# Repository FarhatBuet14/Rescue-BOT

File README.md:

# Rescue-BOT
It is a mechanical system of four wheeled car with two artificial hands. It has also raspberry pi with a pi camera for image processing. The purpose of this project is to rescue human stuck in those places where no search and rescue team can approach. This BOT is built to go to those places all by own and capture a video of the stuck people through identifying human faces. It can also provide any kind of help to that needy people with his artificial hands. The hands are capable of movement with 3 DOF. It is totally a humanitarian project in the manner of rescuing the helpless people where human are unable to approach.

## Watch the [Video][1] (Undergraduate Project)
[1]: https://youtu.be/SeunymHm4Ak

## Updated Version With Hands (We are working on that)

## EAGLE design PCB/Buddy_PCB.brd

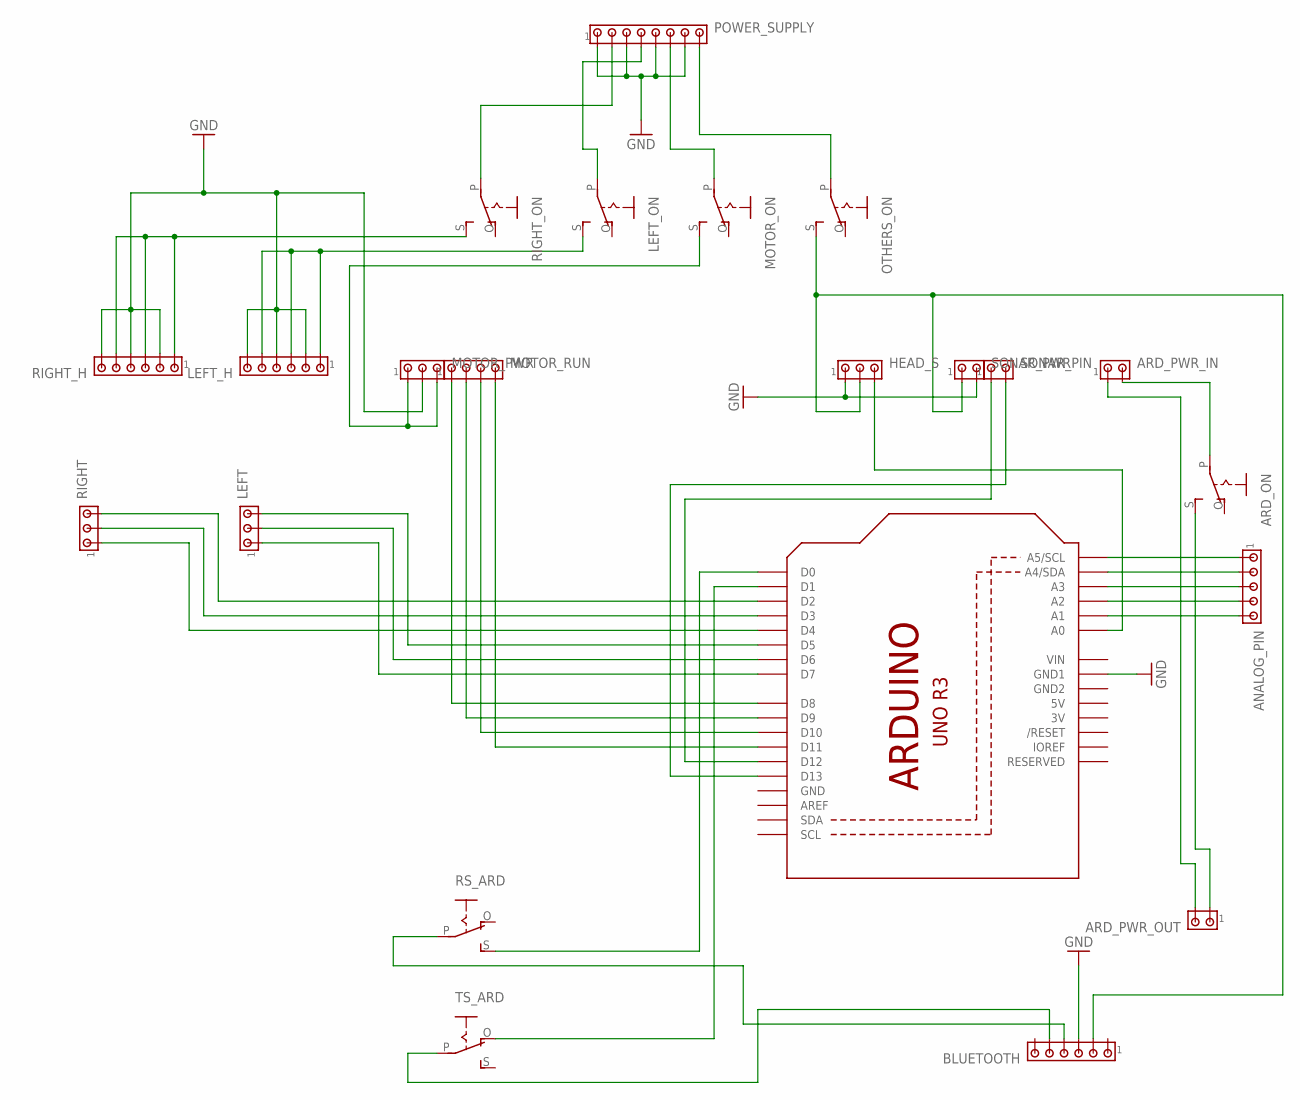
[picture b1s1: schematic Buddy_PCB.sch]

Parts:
ANALOG_PIN: MTA05-100; 10X05MTA
ARD_ON: EG1218S; EG1218
ARD_PWR_IN: MTA02-100; 10X02MTA
ARD_PWR_OUT: MTA02-100; 10X02MTA
BLUETOOTH: MTA06-100; 10X06MTA
HEAD_S: MTA03-100; 10X03MTA
LEFT: MTA03-100; 10X03MTA
LEFT_H: MTA06-100; 10X06MTA
LEFT_ON: EG1218S; EG1218
MOTOR_ON: EG1218S; EG1218
MOTOR_PWR: MTA03-100; 10X03MTA
MOTOR_RUN: MTA04-100; 10X04MTA
OTHERS_ON: EG1218S; EG1218
POWER_SUPPLY: MTA08-100; 10X08MTA
RIGHT: MTA03-100; 10X03MTA
RIGHT_H: MTA06-100; 10X06MTA
RIGHT_ON: EG1218S; EG1218
RS_ARD: EG1218S; EG1218
SONAR_PIN: MTA02-100; 10X02MTA
SONAR_PWR: MTA02-100; 10X02MTA
TS_ARD: EG1218S; EG1218
UNO: ARDUINOR3-DIMENSION; ARDUINOR3

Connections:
3V: UNO.3V
5V: UNO.5V
GND: BLUETOOTH.3, HEAD_S.1, LEFT_H.2, LEFT_H.4, LEFT_H.6, MOTOR_PWR.2, POWER_SUPPLY.1, POWER_SUPPLY.3, POWER_SUPPLY.5, POWER_SUPPLY.7, RIGHT_H.2, RIGHT_H.4, RIGHT_H.6, SONAR_PWR.2, UNO.GND, UNO.GND1
GND2: UNO.GND2
unnamed: RS_ARD.S, UNO.D0
unnamed: TS_ARD.O, UNO.D1
unnamed: RIGHT.3, UNO.D2
unnamed: RIGHT.2, UNO.D3
unnamed: RIGHT.1, UNO.D4
unnamed: LEFT.3, UNO.D5
unnamed: LEFT.2, UNO.D6
unnamed: LEFT.1, UNO.D7
unnamed: MOTOR_RUN.1, UNO.D8
unnamed: MOTOR_RUN.2, UNO.D9
unnamed: MOTOR_RUN.3, UNO.D10
unnamed: MOTOR_RUN.4, UNO.D11
unnamed: SONAR_PIN.1, UNO.D12
unnamed: SONAR_PIN.2, UNO.D13
unnamed: HEAD_S.3, UNO.A0
unnamed: ARD_ON.P, ARD_PWR_IN.2
unnamed: ARD_ON.S, ARD_PWR_OUT.1
unnamed: ARD_PWR_IN.1, ARD_PWR_OUT.2
unnamed: ANALOG_PIN.4, UNO.A2
unnamed: POWER_SUPPLY.2, RIGHT_ON.P
unnamed: LEFT_ON.P, POWER_SUPPLY.4
unnamed: MOTOR_ON.P, POWER_SUPPLY.6
unnamed: OTHERS_ON.P, POWER_SUPPLY.8
unnamed: RIGHT_H.1, RIGHT_H.3, RIGHT_H.5, RIGHT_ON.S
unnamed: LEFT_H.1, LEFT_H.3, LEFT_H.5, LEFT_ON.S
unnamed: MOTOR_ON.S, MOTOR_PWR.1, MOTOR_PWR.3
unnamed: BLUETOOTH.2, HEAD_S.2, OTHERS_ON.S, SONAR_PWR.1
unnamed: BLUETOOTH.4, RS_ARD.P
unnamed: BLUETOOTH.5, TS_ARD.P
unnamed: ANALOG_PIN.1, UNO.A5 (A5/SCL)
unnamed: ANALOG_PIN.2, UNO.A4 (A4/SDA)
unnamed: ANALOG_PIN.3, UNO.A3
unnamed: ANALOG_PIN.5, UNO.A1
VIN: UNO.VIN

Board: 2 copper layers, 22 parts (1 on the bottom side), 34 nets, no tracks yet.

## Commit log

2019-12-23 GIF Upload
2019-12-23 Add the images
2019-12-23 Final Release
2019-12-23 Add Cost Description
2019-12-23 Final Image Release
